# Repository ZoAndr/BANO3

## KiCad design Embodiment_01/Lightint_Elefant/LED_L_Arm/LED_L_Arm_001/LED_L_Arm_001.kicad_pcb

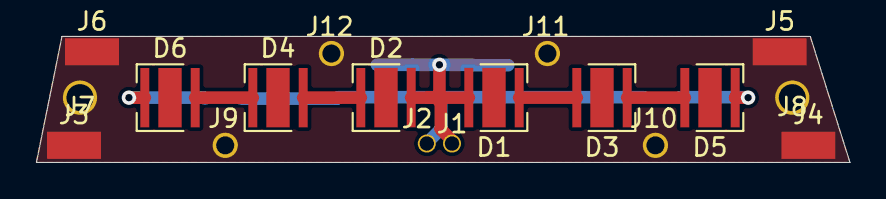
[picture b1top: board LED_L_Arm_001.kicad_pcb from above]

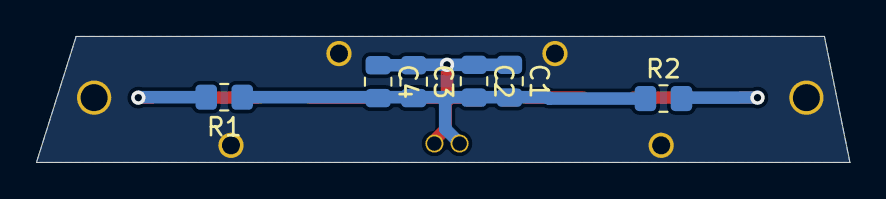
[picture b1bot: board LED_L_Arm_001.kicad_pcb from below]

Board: 2 copper layers, 45.2 x 7.0 mm, 24 parts (6 on the bottom side), 9 nets.

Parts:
C1, C2, C3, C4: C; R_0805_2012Metric
D1, D2, D3, D4, D5, D6: LED; LED_Cree-XHP35
J1, J2: Conn_01x01_Female; pin_0.8
J3, J4, J5, J6: Conn_01x01_Female; WireSidePlate_001
J7, J8: Conn_01x01_Female; pin_1.5
J9, J10, J11, J12: Conn_01x01_Female; pin_1.0
R1, R2: R; R_0805_2012Metric_Pad1.20x1.40mm_HandSolder

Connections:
GND: J3.1, J4.1, J5.1, J6.1, J7.1, J8.1, J9.1, J10.1, J11.1, J12.1
unnamed: C1.1, C2.1, C3.1, C4.1, D1.2, D2.2, J1.1
unnamed: C1.2, C2.2, C3.2, C4.2, J2.1, R1.1, R2.1
unnamed: D1.1, D3.2
unnamed: D2.1, D4.2
unnamed: D3.1, D5.2
unnamed: D4.1, D6.2
unnamed: D5.1, R1.2
unnamed: D6.1, R2.2

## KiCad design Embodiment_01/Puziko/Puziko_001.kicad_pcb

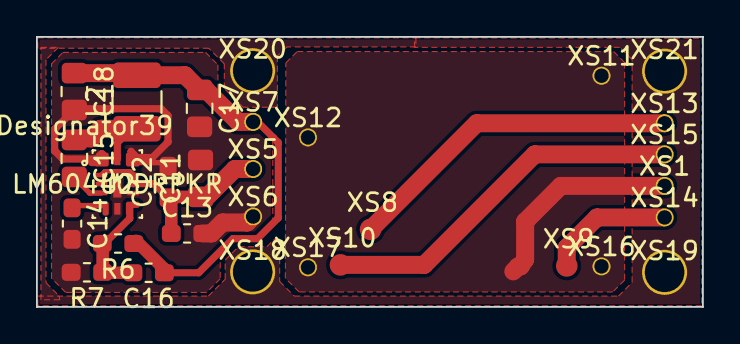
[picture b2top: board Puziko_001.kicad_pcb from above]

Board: 2 copper layers, 37.0 x 15.0 mm, 30 parts (0 on the bottom side), 11 nets.

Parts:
C11, C15, C17, C18: C; C_0805_2012Metric_Pad1.15x1.40mm_HandSolder
C12, C13, C14, C16: C; C_0603_1608Metric_Pad1.05x0.95mm_HandSolder
L2: L; L_1210_3225Metric_Pad1.42x2.65mm_HandSolder
R6: R; R_0603_1608Metric_Pad1.05x0.95mm_HandSolder
R7: R; L_0603_1608Metric_Pad1.05x0.95mm_HandSolder
U2: LM60440DRPKR
XS1, XS5, XS6, XS7, XS11, XS12, XS13, XS14, XS15, XS16, XS17: Pin_0.5; pin_0.8
XS8, XS9, XS10: Pin_0.5; Plate_1
XS18, XS19, XS20, XS21: Pin_0.5; pin_2.2

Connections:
GND: C11.2, C12.2, C13.2, C14.2, C17.2, C18.2, R7.2, U2.1, U2.6, U2.8, U2.11, U2.13, XS1.1, XS6.1, XS11.1, XS12.1, XS16.1, XS17.1
unnamed: C11.1, C12.1, C13.1, U2.2, U2.9, U2.10, XS5.1
unnamed: C14.1, U2.5
unnamed: C15.1, L2.1, U2.12
unnamed: C15.2, U2.4
unnamed: C16.1, C17.1, C18.1, L2.2, R6.1, XS7.1
unnamed: C16.2, R6.2, R7.1, U2.7
unnamed: XS10.1, XS15.1
unnamed: XS8.1, XS13.1
unnamed: XS9.1, XS14.1
unnamed: XS18.1, XS19.1, XS20.1, XS21.1

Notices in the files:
parts and their libraries:
Copyright 2021 Accelerated Designs. All rights reserved.
